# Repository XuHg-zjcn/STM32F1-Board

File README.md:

# PCB描述
## 主芯片
STM32F103C8T6  LQFP48  
RAM 20kB, Flash 64kB  

## 板载元件
- 电源 : AMS1117-3.3 滤波电容47u 104
- 电池 : CR1220, 104电容
- 晶振 :  8M, 32.768K, 负载电容, 负载电阻

## 用户交互
- 按钮 : NRST, WKUP, KPA0
- LED  : 红绿双色(PC13, 一个引脚驱动两个LED)
- OLED : I2C四针插口J9

## 接口
|标识| 名称|描述                          |
|:--:|:---:|:-----------------------------|
| J1 |USB  |microUSB接口                  |
| J2 |电源 |GND 3V3 5V 每种电压有4个针    |
| J3 |SWD  |顺序为GND SWCLK SWDIO 3V3 5V, 是为了兼容其他的板子|
| J4 |保护 |USB, SWD, BOOT0               |
| J5 |ADC  |有10个通道                    |
| J6 |SPI1 |用户, 与ADC 4,5,6,7重叠       |
| J7 |UART1|用户,  并入PA8引脚            |
| J8 |I2C1 |用户                          |
| J9 |I2C2 |液晶屏, 并入PB2引脚           |
|J10 |SPI2 |有保护罩, 已经连接microSD     |
|J11 |SD   |microSD卡槽                   |

## 未来计划
配件组合:  
- 电池: CR1220 / 3.7V锂电池(二选一)
- 储存: microSD / SPI Flash(二选一), I2C EEPROM(可选)

# 本项目规范
除了引脚编号，其他单根线的标签文字统一使用0.15mm宽度，多根线统一使用0.2mm宽度文字。

电源0.29mm

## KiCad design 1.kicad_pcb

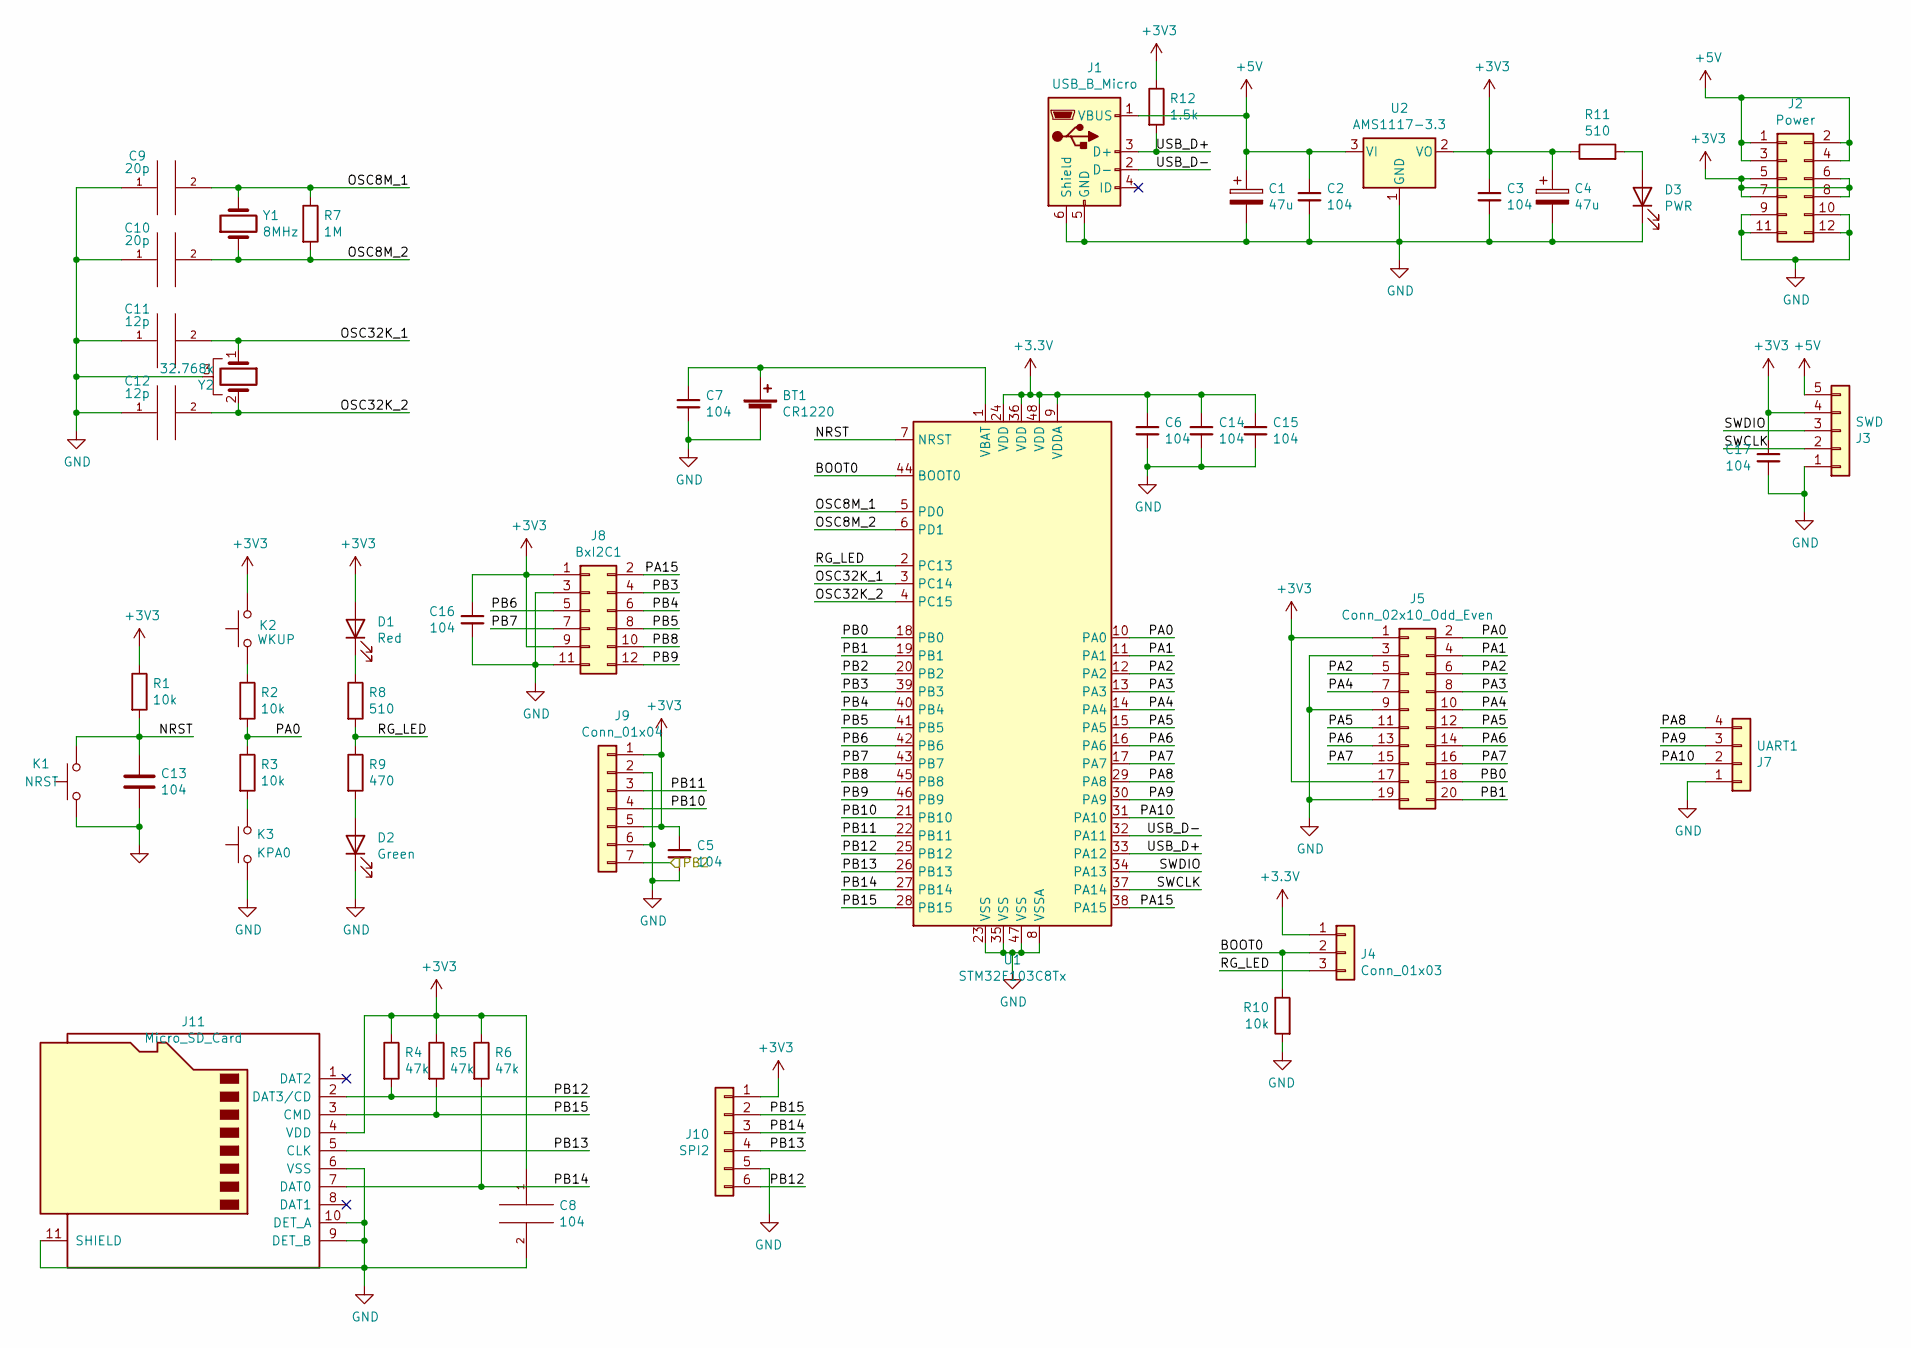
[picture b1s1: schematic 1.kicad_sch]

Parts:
BT1: CR1220; BatteryHolder_Keystone_3001_1x12mm
C1, C4: 47u; C_1206_3216Metric
C2, C3, C5, C6, C7, C8, C13, C14, C15, C16, C17: 104; C_0603_1608Metric
C9, C10: 20p; C_0603_1608Metric
C11, C12: 12p; C_0603_1608Metric
D1: Red; LED_0603_1608Metric
D2: Green; LED_0603_1608Metric
D3: PWR; LED_0603_1608Metric
J1: USB_B_Micro; USB_Micro-B_GCT_USB3076-30-A
J2: Power; PinHeader_2x06_P2.54mm_Vertical
J3: SWD; PinHeader_1x05_P2.54mm_Horizontal
J4: Conn_01x03; PinHeader_1x03_P2.54mm_Vertical
J5: Conn_02x10_Odd_Even; PinHeader_2x10_P2.54mm_Vertical
J7: UART1; PinHeader_1x04_P2.54mm_Vertical
J8: BxI2C1; PinHeader_2x06_P2.54mm_Vertical
J9: Conn_01x04; PinSocket_1x07_P2.54mm_Vertical
J10: SPI2; PinSocket_1x06_P2.54mm_Vertical
J11: Micro_SD_Card; microSD_HC_Hirose_DM3BT-DSF-PEJS
K1: NRST; SW_Push_SPST_NO_Alps_SKRK
K2: WKUP; SW_Push_SPST_NO_Alps_SKRK
K3: KPA0; SW_Push_SPST_NO_Alps_SKRK
R1, R2, R3, R10: 10k; R_0603_1608Metric
R4, R5, R6: 47k; R_0603_1608Metric
R7: 1M; R_0603_1608Metric
R8, R11: 510; R_0603_1608Metric
R9: 470; R_0603_1608Metric
R12: 1.5k; R_0603_1608Metric
U1: STM32F103C8Tx; LQFP-48_7x7mm_P0.5mm
U2: AMS1117-3.3; SOT-223-3_TabPin2
Y1: 8MHz; Crystal_SMD_HC49-SD
Y2: 32.768k; Crystal_DS26_D2.0mm_L6.0mm_Horizontal_1EP_style1

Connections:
+5V: C1.1, C2.1, J1.1 (VBUS), J2.1, J2.2, J2.3, J2.4, J3.5, U2.3 (VI)
/BOOT0: J4.2, R10.1, U1.44 (BOOT0)
/NRST: C13.1, K1.2, R1.2, U1.7 (NRST)
/OSC8M_1: C9.2, R7.1, U1.5 (PD0), Y1.2
/OSC8M_2: C10.2, R7.2, U1.6 (PD1), Y1.1
/OSC32K_1: C11.2, U1.3 (PC14), Y2.1
/OSC32K_2: C12.2, U1.4 (PC15), Y2.2
/PA0: J5.2, R2.2, R3.1, U1.10 (PA0)
/PA1: J5.4, U1.11 (PA1)
/PA2: J5.5, J5.6, U1.12 (PA2)
/PA3: J5.8, U1.13 (PA3)
/PA4: J5.7, J5.10, U1.14 (PA4)
/PA5: J5.11, J5.12, U1.15 (PA5)
/PA6: J5.13, J5.14, U1.16 (PA6)
/PA7: J5.15, J5.16, U1.17 (PA7)
/PA8: J7.4, U1.29 (PA8)
/PA9: J7.3, U1.30 (PA9)
/PA10: J7.2, U1.31 (PA10)
/PA15: J8.2, U1.38 (PA15)
/PB0: J5.18, U1.18 (PB0)
/PB1: J5.20, U1.19 (PB1)
/PB2: J9.7, U1.20 (PB2)
/PB3: J8.4, U1.39 (PB3)
/PB4: J8.6, U1.40 (PB4)
/PB5: J8.8, U1.41 (PB5)
/PB6: J8.5, U1.42 (PB6)
/PB7: J8.7, U1.43 (PB7)
/PB8: J8.10, U1.45 (PB8)
/PB9: J8.12, U1.46 (PB9)
/PB10: J9.4, U1.21 (PB10)
/PB11: J9.3, U1.22 (PB11)
/PB12: J10.6, J11.2 (DAT3/CD), R4.2, U1.25 (PB12)
/PB13: J10.4, J11.5 (CLK), U1.26 (PB13)
/PB14: J10.3, J11.7 (DAT0), R6.2, U1.27 (PB14)
/PB15: J10.2, J11.3 (CMD), R5.2, U1.28 (PB15)
/RG_LED: J4.3, R8.2, R9.1, U1.2 (PC13)
/SWCLK: J3.2, U1.37 (PA14)
/SWDIO: J3.3, U1.34 (PA13)
/USB_D+: J1.3 (D+), R12.2, U1.33 (PA12)
/USB_D-: J1.2 (D-), U1.32 (PA11)
GND: BT1.2 (-), C1.2, C2.2, C3.2, C4.2, C5.2, C6.2, C7.2, C8.2, C9.1, C10.1, C11.1, C12.1, C13.2, C14.2, C15.2, C16.2, C17.2, D2.1 (K), D3.1 (K), J1.5 (GND), J1.6 (Shield), J2.9, J2.10, J2.11, J2.12, J3.1, J5.3, J5.9, J5.19, J7.1, J8.3, J8.11, J9.2, J9.6, J10.5, J11.6 (VSS), J11.9 (DET_B), J11.10 (DET_A), J11.11 (SHIELD), K1.1, K3.1, R10.2, U1.8 (VSSA), U1.23 (VSS), U1.35 (VSS), U1.47 (VSS), U2.1 (GND), Y2.3
unnamed: BT1.1 (+), C7.1, U1.1 (VBAT)
unnamed: D1.1 (K), R8.1
unnamed: D2.2 (A), R9.2
unnamed: D3.2 (A), R11.2
unnamed: K2.1, R2.1
unnamed: K3.2, R3.2

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
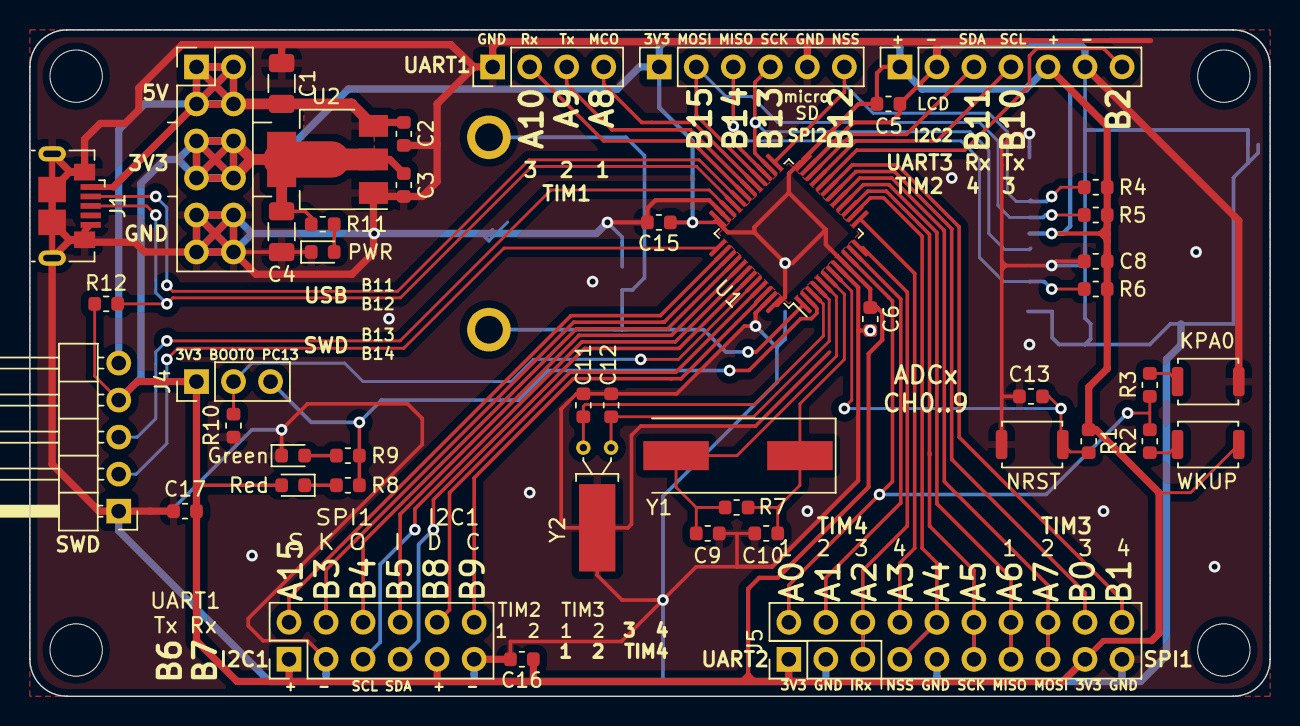
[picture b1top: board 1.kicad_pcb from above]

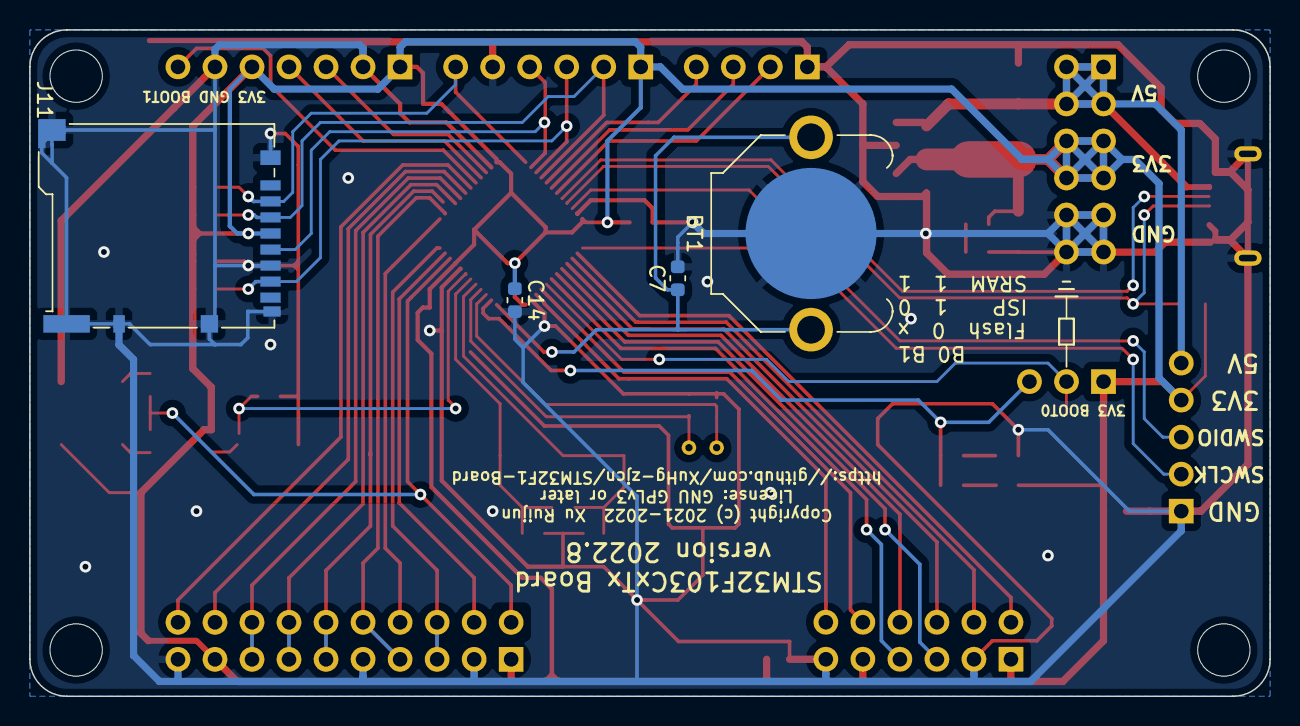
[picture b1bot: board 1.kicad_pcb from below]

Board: 2 copper layers, 85.1 x 45.7 mm, 50 parts (4 on the bottom side), 48 nets.

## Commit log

2021-05-02 move U1(STM32 Chip)
2021-05-02 move edge
2021-05-02 movdify some line
2021-05-02 gnd line
2021-05-02 op lines
2021-05-02 resize edge
2021-05-02 op gnd line
2021-05-02 fix DRC warings
2021-05-02 operate line near edge
2021-05-02 fix: ADC channel no connect
2021-05-02 label two colors
2021-05-03 labels
2021-05-03 SD ground
2021-05-03 fix lines
2021-05-03 fix lines2
2021-05-04 fix: 32.768k OSC pin
2021-05-04 fix: power line
2021-05-04 add 104 caps
2021-05-04 use 2x6 header for BxI2C1
2021-05-04 I2C1 line
2021-05-04 abc123
2021-05-04 5V line on 1206 cap
2021-05-04 GND line under battary
2021-05-04 fix: edge
2021-05-04 fix: usb GND对称性
2021-05-04 fix: GND line on VSSA cap
2021-05-04 fix: 3.3V line near edge
2021-05-04 fill area
2021-05-04 add gitignore
2021-05-04 silks layer
2021-05-04 KPA0
2021-05-04 move pin headers on 原理图
2021-05-04 rename label to PAxx/PBxx on 原理图
2021-05-04 添加不连接标签
2021-05-04 使用网络标签代替层次标签
2021-05-04 移动PCB标签
2021-05-04 修改原理图字段，并修改PCB
2021-05-04 修改字段2
2021-05-04 填充GND
2021-05-04 修复靠近边缘的线突出
2021-05-04 BOOT0标签
2021-05-04 压缩按钮空间
2021-05-04 SD卡槽连接
2021-05-04 move C11,C12 label
2021-05-05 移除无用的过孔
2021-05-05 label of SWD port
2021-05-05 usb port lines
2021-05-05 move usb
2021-05-05 usb port GND line
2021-05-05 lines op2
2021-05-05 SWD,3V3 lines
2021-05-05 fill GND
2021-05-05 move label B6,B7
2021-05-05 move label of PinHeaders
2021-05-05 line of PA4
2021-05-05 fix GND near to fill
2021-05-05 add label "STM32F103C8T6 Board, by XuRuijun, QQ 1687701765"
2021-05-06 USB GND线
2021-05-06 MCU pin 36 connect to 3.3V
2021-05-06 move 32.768k OSC
2021-05-06 op power lines
2021-05-06 op power lines2
2021-05-06 op power lines3
2021-05-06 bat line
2021-05-06 op power line4
2021-05-06 op power line5
2021-05-06 op lines 6
2021-05-06 op GND line near USB
2021-05-06 USB信号线过孔附件倒角
2021-05-06 J4 USB信号线离焊盘太近
2021-05-06 边缘GND线
2021-05-06 晶振线路
2021-05-06 调整晶振位置
2021-05-06 晶振使用0.2mm线
2021-05-06 晶振使用0.2mm线-2
2021-05-07 MCU左上角三个通孔
2021-05-07 填充GN
2021-05-07 move labels
2021-05-07 GND line near microSD card
2021-05-07 add PinSocket
2021-05-07 coner hole, 3.3V line near microSD card
2021-05-07 save .sch file
2021-05-07 op in windows
2021-05-08 重新布线，取消SWD和USB排针
2021-05-08 move usb and swd line insert gnd between
2021-05-08 fill and via
2021-05-08 move via
2021-05-08 op via holes
2021-05-08 op via holes2
2021-05-08 op via holes3
2021-05-08 USB D+ 1.5k up res, 104 cap near SWD
2021-05-08 op power lines 0.29mm
2021-05-08 relink GND line near 32.768k OSC
2021-05-08 添加禁布区，清除104电容的覆盖铜
2021-05-08 视频中修改
2021-05-08 tran 90deg
2021-05-08 convert_inv.py
2021-05-08 lines near power PinHeader
2021-05-08 line wider to 0.5mm, move micro sd lines
2021-05-08 优化microSD走线，加了两个过孔
2021-05-08 优化microSD走线，3.3V电源线
2021-05-08 移动板子与50mil网格重合
2021-05-09 12312
2021-05-09 PC13 replace I2C1 one of 3V3
2021-05-15 copy from windows, 成功打样
2021-06-30 edit
2021-06-30 2x10 pins
2021-06-30 add line on silks layer
2021-06-30 conver Cu
2021-06-30 save 1.sch
2022-08-25 提交遗留内容
2022-08-25 fix: 把J5放置在正面
2022-08-25 update to KiCad 6
2022-08-26 add 1-cache.lib, 1-rescue.lib, 1-resume.dcm, update README.md
2022-08-26 添加GPLv3许可证并应用，GitHub仓库网址，移除"JLCJLCJLCJLC"
2022-08-26 "文档"和"规范.txt"合并为"README.md"
2022-08-26 提交图片并插入README.md

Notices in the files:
1.kicad_pcb:
Copyright (c) 2021-2022  Xu Ruijun
License: GNU GPLv3 or later
